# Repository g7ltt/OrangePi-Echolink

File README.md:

# OrangePi Echolink
Echolink transceiver for the Orange Pi

Install any version of Linux and also SVXLink as the Echolink client.

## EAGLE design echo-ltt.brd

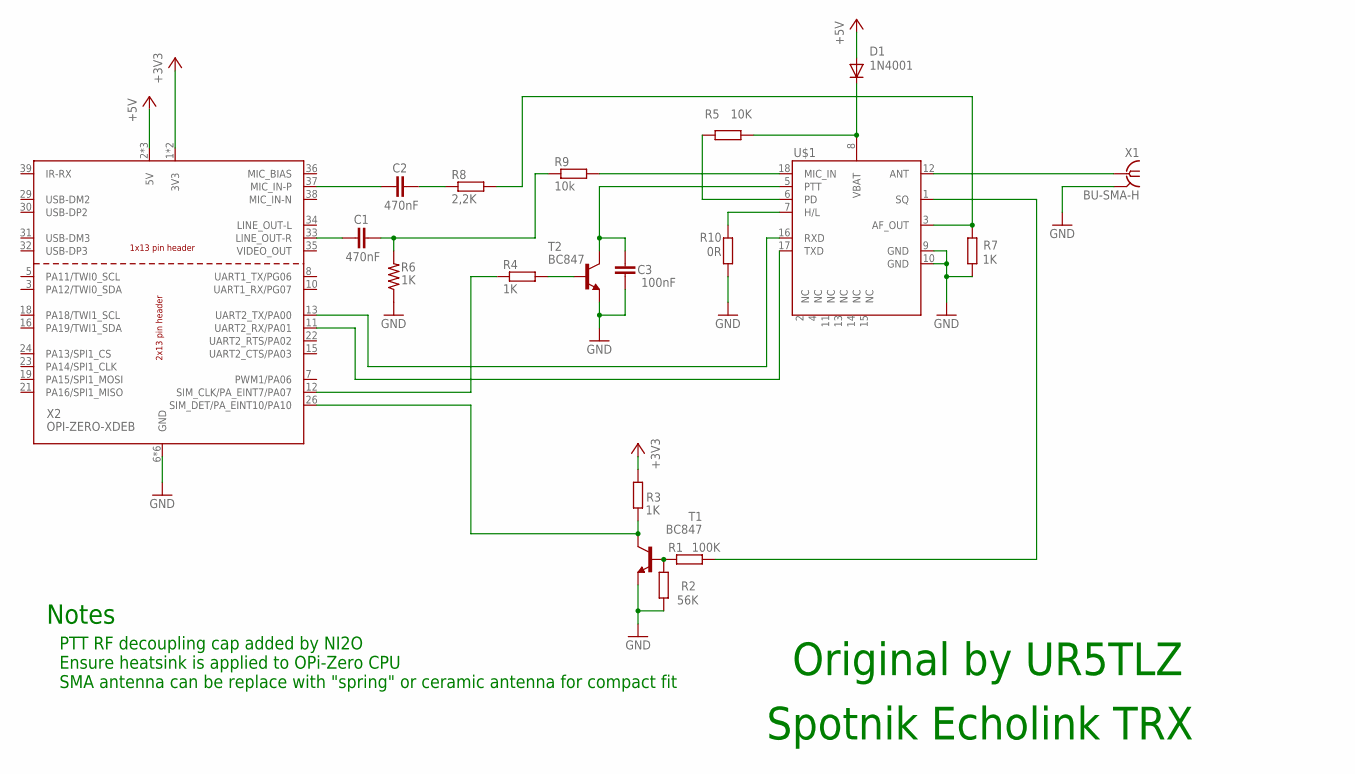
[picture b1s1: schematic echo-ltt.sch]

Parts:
C1, C2: 470nF; C0805
C3: 100nF; C0805
D1: 1N4001; DO41-10
R1: 100K; R0805
R2: 56K; R0805
R3, R4, R6, R7: 1K; R0805
R5: 10K; R0805
R8: 2,2K; R0805
R9: 10k; R0805
R10: 0R; R0805
T1, T2: BC847; SOT23
U$1: DRA818A
X1: BU-SMA-H
X2: OPI-ZERO-XDEB; OPIOHATDEB

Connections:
+3V3: R3.2, X2.1 (3V3), X2.17 (3V3)
+5V: D1.A, X2.2 (5V), X2.4 (5V), X2.27 (5V)
GND: C3.2, R2.1, R6.1, R7.1, R10.1, T1.2 (E), T2.2 (E), U$1.9 (GND), U$1.10 (GND), X1.2, X1.3 (2), X1.4 (2), X1.5 (2), X2.6 (GND), X2.9 (GND), X2.14 (GND), X2.20 (GND), X2.25 (GND), X2.28 (GND)
unnamed: U$1.12 (ANT), X1.1
unnamed: R1.2, R2.2, T1.1 (B)
unnamed: R3.1, T1.3 (C), X2.26 (SIM_DET/PA_EINT10/PA10)
unnamed: D1.C, R5.1, U$1.8 (VBAT)
unnamed: R1.1, U$1.1 (SQ)
unnamed: R4.2, T2.1 (B)
unnamed: C3.1, T2.3 (C), U$1.5 (PTT)
unnamed: R4.1, X2.12 (SIM_CLK/PA_EINT7/PA07)
unnamed: R5.2, U$1.6 (PD)
unnamed: C1.2, X2.33 (LINE_OUT-R)
unnamed: C1.1, R6.2, R9.1
unnamed: R7.2, R8.2, U$1.3 (AF_OUT)
unnamed: C2.1, R8.1
unnamed: C2.2, X2.37 (MIC_IN-P)
unnamed: U$1.17 (TXD), X2.11 (UART2_RX/PA01)
unnamed: U$1.16 (RXD), X2.13 (UART2_TX/PA00)
unnamed: R9.2, U$1.18 (MIC_IN)
unnamed: R10.2, U$1.7 (H/L)

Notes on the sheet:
Spotnik Echolink TRX
Original by UR5TLZ
PTT RF decoupling cap added by NI2O Ensure heatsink is applied to OPi-Zero CPU SMA antenna can be replace with "spring" or ceramic antenna for compact fit
Notes

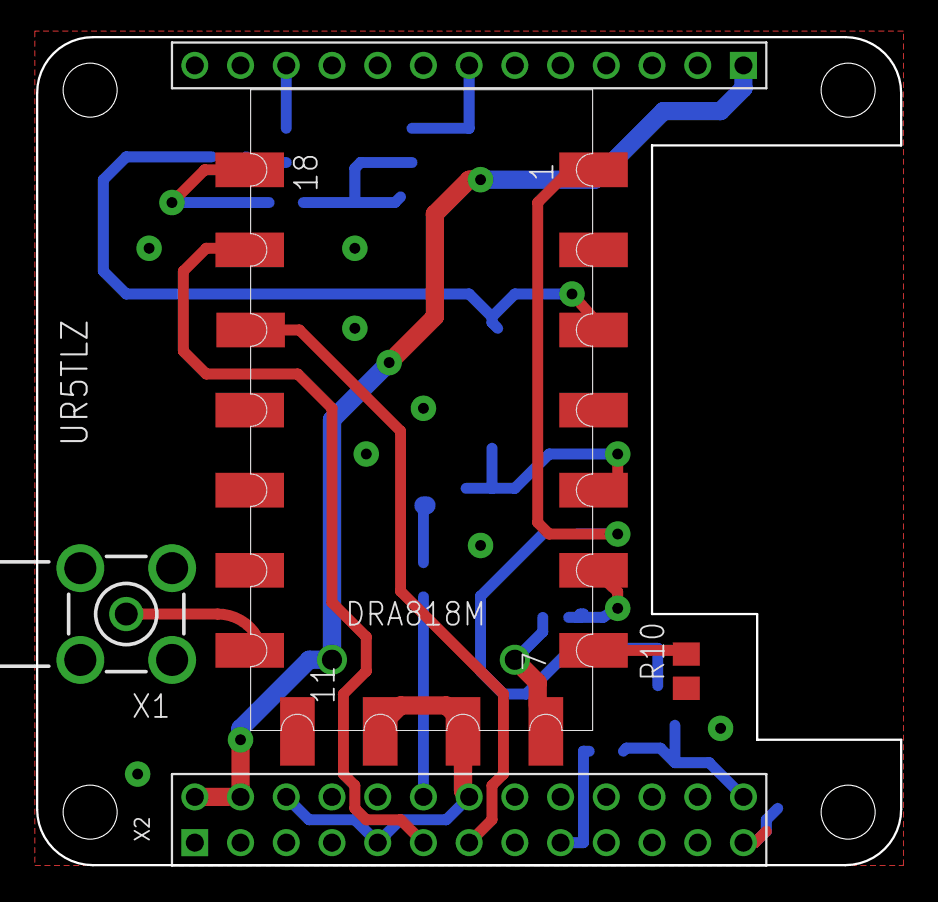
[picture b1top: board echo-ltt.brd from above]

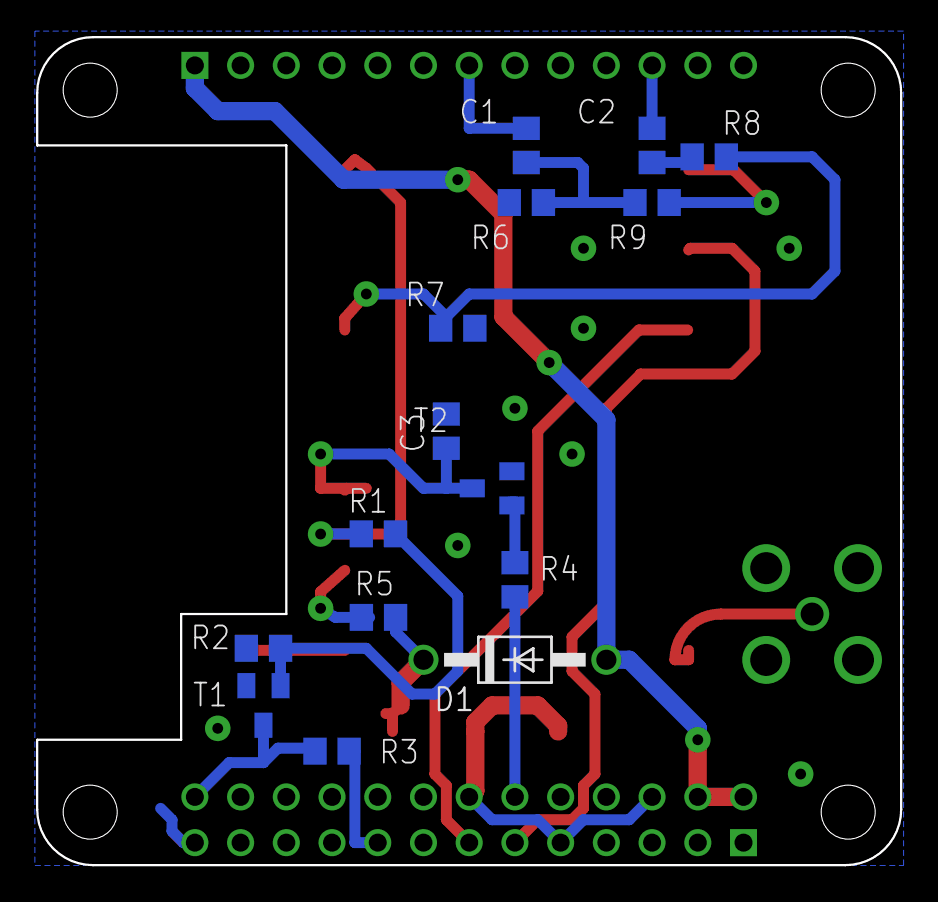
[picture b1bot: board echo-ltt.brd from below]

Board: 2 copper layers, 48.0 x 46.0 mm, 19 parts (15 on the bottom side), 21 nets.

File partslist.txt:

Partlist

Exported from echo.sch at 4/21/2019 12:52

EAGLE Version 9.3.2 Copyright (c) 1988-2019 Autodesk, Inc.

Assembly variant: 

Part     Value          Device        Package    Library    Sheet

C1       470nF          C-EUC0805     C0805      resistor   1
C2       470nF          C-EUC0805     C0805      resistor   1
C3       100nF          C-EUC0805     C0805      resistor   1
D1       1N4001         DIODE-DO41-10 DO41-10    diode      1
R1       100K           R-EU_R0805    R0805      resistor   1
R2       56K            R-EU_R0805    R0805      resistor   1
R3       1K             R-EU_R0805    R0805      resistor   1
R4       1K             R-EU_R0805    R0805      resistor   1
R5       10K            R-EU_R0805    R0805      resistor   1
R6       1K             R-US_R0805    R0805      resistor   1
R7       1K             R-EU_R0805    R0805      resistor   1
R8       2,2K           R-EU_R0805    R0805      resistor   1
R9       10k            R-EU_R0805    R0805      resistor   1
R10      0R             R-EU_R0805    R0805      resistor   1
T1       BC847          BC847         SOT23      transistor 1
T2       BC847          BC847         SOT23      transistor 1
U$1                     DRA818A       DRA818A    dorji      1
X1       BU-SMA-H       BU-SMA-H      BU-SMA-H   con-coax   1
X2       OPI-ZERO-XDEB  OPI-ZERO-XDEB OPIOHATDEB OrangePi0  1
